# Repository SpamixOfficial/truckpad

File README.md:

# The Truckpad - Ready for Calais /:\

Ever been driving your truck in ETS2 and realized that:
1. You have too few buttons for your 6 different types of honks?
2. Using a g29-scroll wheel to switch menu tab is janky?

Well oh boy do I have the solution for you! 

The Truckpad is a macropad specifically designed with these problems in mind. It has 4 switches + a modifier switch, which in total allows for up to 8 macros on the switches alone!

But this isn't enough (of course)...

You also need to be able to change tabs and do easy confirmation when fueling, so of course there's a rotary encoder to solve just that. It is also placed with your hand position in mind, so you don't have to do weird finger stretching to use it!

Last but not least it has an OLED screen where you can display information such as your nearest city in ETS2, or whatever you like really, the sky (and ETS2 modding capabilities ) is your limits!

Configuration is done in VIA, so no need to recompile the firmware!

The whole thing also comes in a small form factor so that's nice :D

**Here's also a list of features, in case you don't feel like reading all that!**

## Features 
- 4 switches + 1 modifier switch (toggle) - up to 8 macros!
- Rotary encoder WITH switch placed in an optimal position for your fingers, makes navigation easy in the ETS2 menu tab
- 128*32px OLED screen, display whatever information you like!
- QMK+VIA easy configuration - never been easier to configure huh?
- Debugging? We got a status LED for that :D

## BOM
- 5x Cherry MX Switches
- 2x SK6812 MINI Leds
- 1x XIAO RP2040
- 5x Blank DSA Keycaps
- 4x M3x16 Bolt
- 4x M3 Heatset
- 1x EC11 rotary encoder with switch
- 1x I2C OLED 128x32px

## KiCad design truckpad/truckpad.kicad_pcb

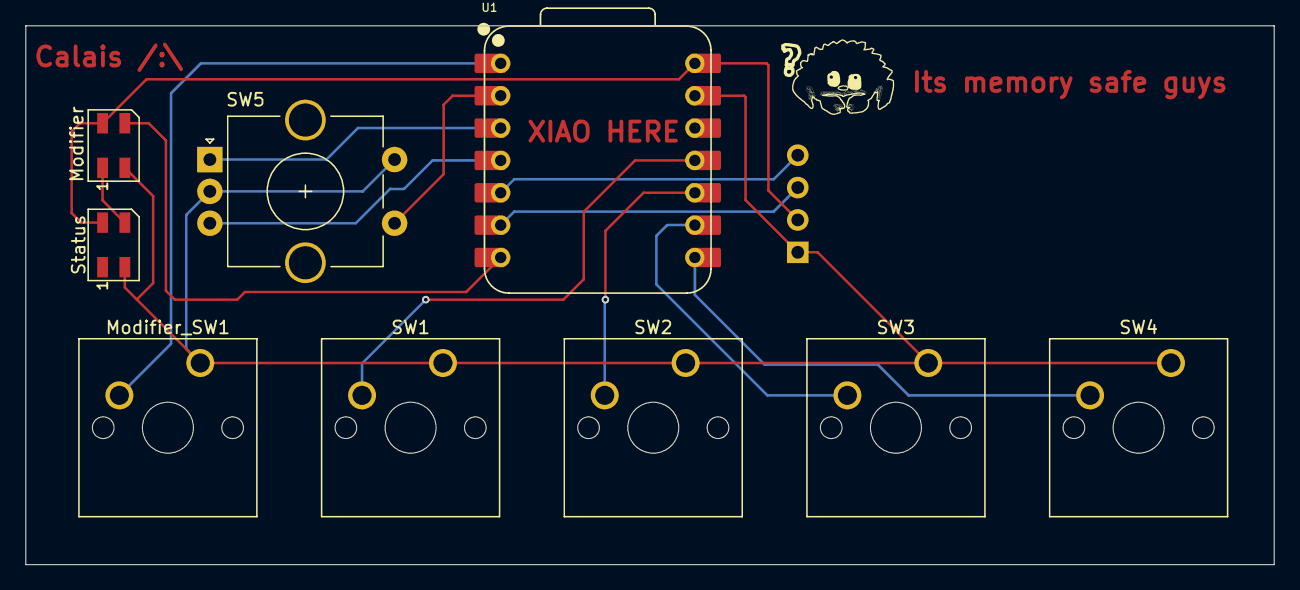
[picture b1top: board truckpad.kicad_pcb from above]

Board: 2 copper layers, 98.0 x 42.3 mm, 10 parts (0 on the bottom side), 14 nets.

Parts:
J1: OLED-128x32
Modifier: SK6812MINI; LED_SK6812MINI_PLCC4_3.5x3.5mm_P1.75mm
Modifier_SW1: SW_Push; SW_Cherry_MX_1.00u_PCB
SW1, SW2, SW3, SW4: SW_Push; SW_Cherry_MX_1.00u_PCB
SW5: RotaryEncoder_Switch; RotaryEncoder_Alps_EC11E-Switch_Vertical_H20mm_CircularMoun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
Status: SK6812MINI; LED_SK6812MINI_PLCC4_3.5x3.5mm_P1.75mm
U1: XIAO-RP2040-DIP

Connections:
+5V: J1.2 (VCC), Modifier.4 (VDD), Status.4 (VDD), U1.14 (VBUS)
GND: J1.1 (GND), Modifier.2 (VSS), Modifier_SW1.1, SW1.1, SW2.1, SW3.1, SW4.1, SW5.C, SW5.S2, Status.2 (VSS), U1.13 (GND)
unnamed: J1.3 (SCL), U1.6 (GPIO7/SCL)
unnamed: J1.4 (SDA), U1.5 (GPIO6/SDA)
unnamed: Modifier.3 (DIN), U1.7 (GPIO0/TX)
unnamed: Modifier.1 (DOUT), Status.3 (DIN)
unnamed: SW4.2, U1.8 (GPIO1/RX)
unnamed: SW3.2, U1.9 (GPIO2/SCK)
unnamed: SW1.2, U1.11 (GPIO3/MOSI)
unnamed: SW2.2, U1.10 (GPIO4/MISO)
unnamed: Modifier_SW1.2, U1.1 (GPIO26/ADC0/A0)
unnamed: SW5.S1, U1.2 (GPIO27/ADC1/A1)
unnamed: SW5.A, U1.3 (GPIO28/ADC2/A2)
unnamed: SW5.B, U1.4 (GPIO29/ADC3/A3)

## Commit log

2025-05-24 Initial commit (pcb done)
2025-05-25 Organizing, prepping for submission
2025-06-06 WOah it compiles now
2025-06-06 Okay everything is set up now
2025-06-06 Via support
